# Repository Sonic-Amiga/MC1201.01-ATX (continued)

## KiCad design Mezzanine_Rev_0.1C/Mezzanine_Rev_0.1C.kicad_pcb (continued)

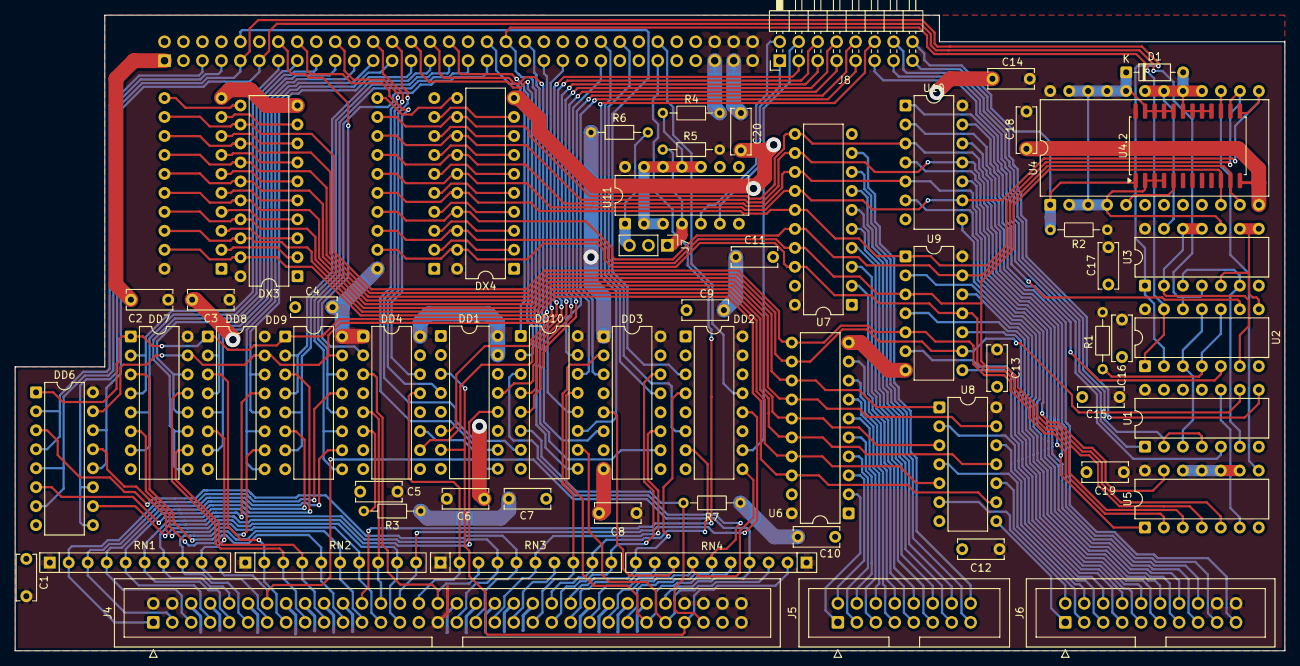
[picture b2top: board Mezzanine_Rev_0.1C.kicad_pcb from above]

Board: 2 copper layers, 170.0 x 85.1 mm, 63 parts (1 on the bottom side), 174 nets.
